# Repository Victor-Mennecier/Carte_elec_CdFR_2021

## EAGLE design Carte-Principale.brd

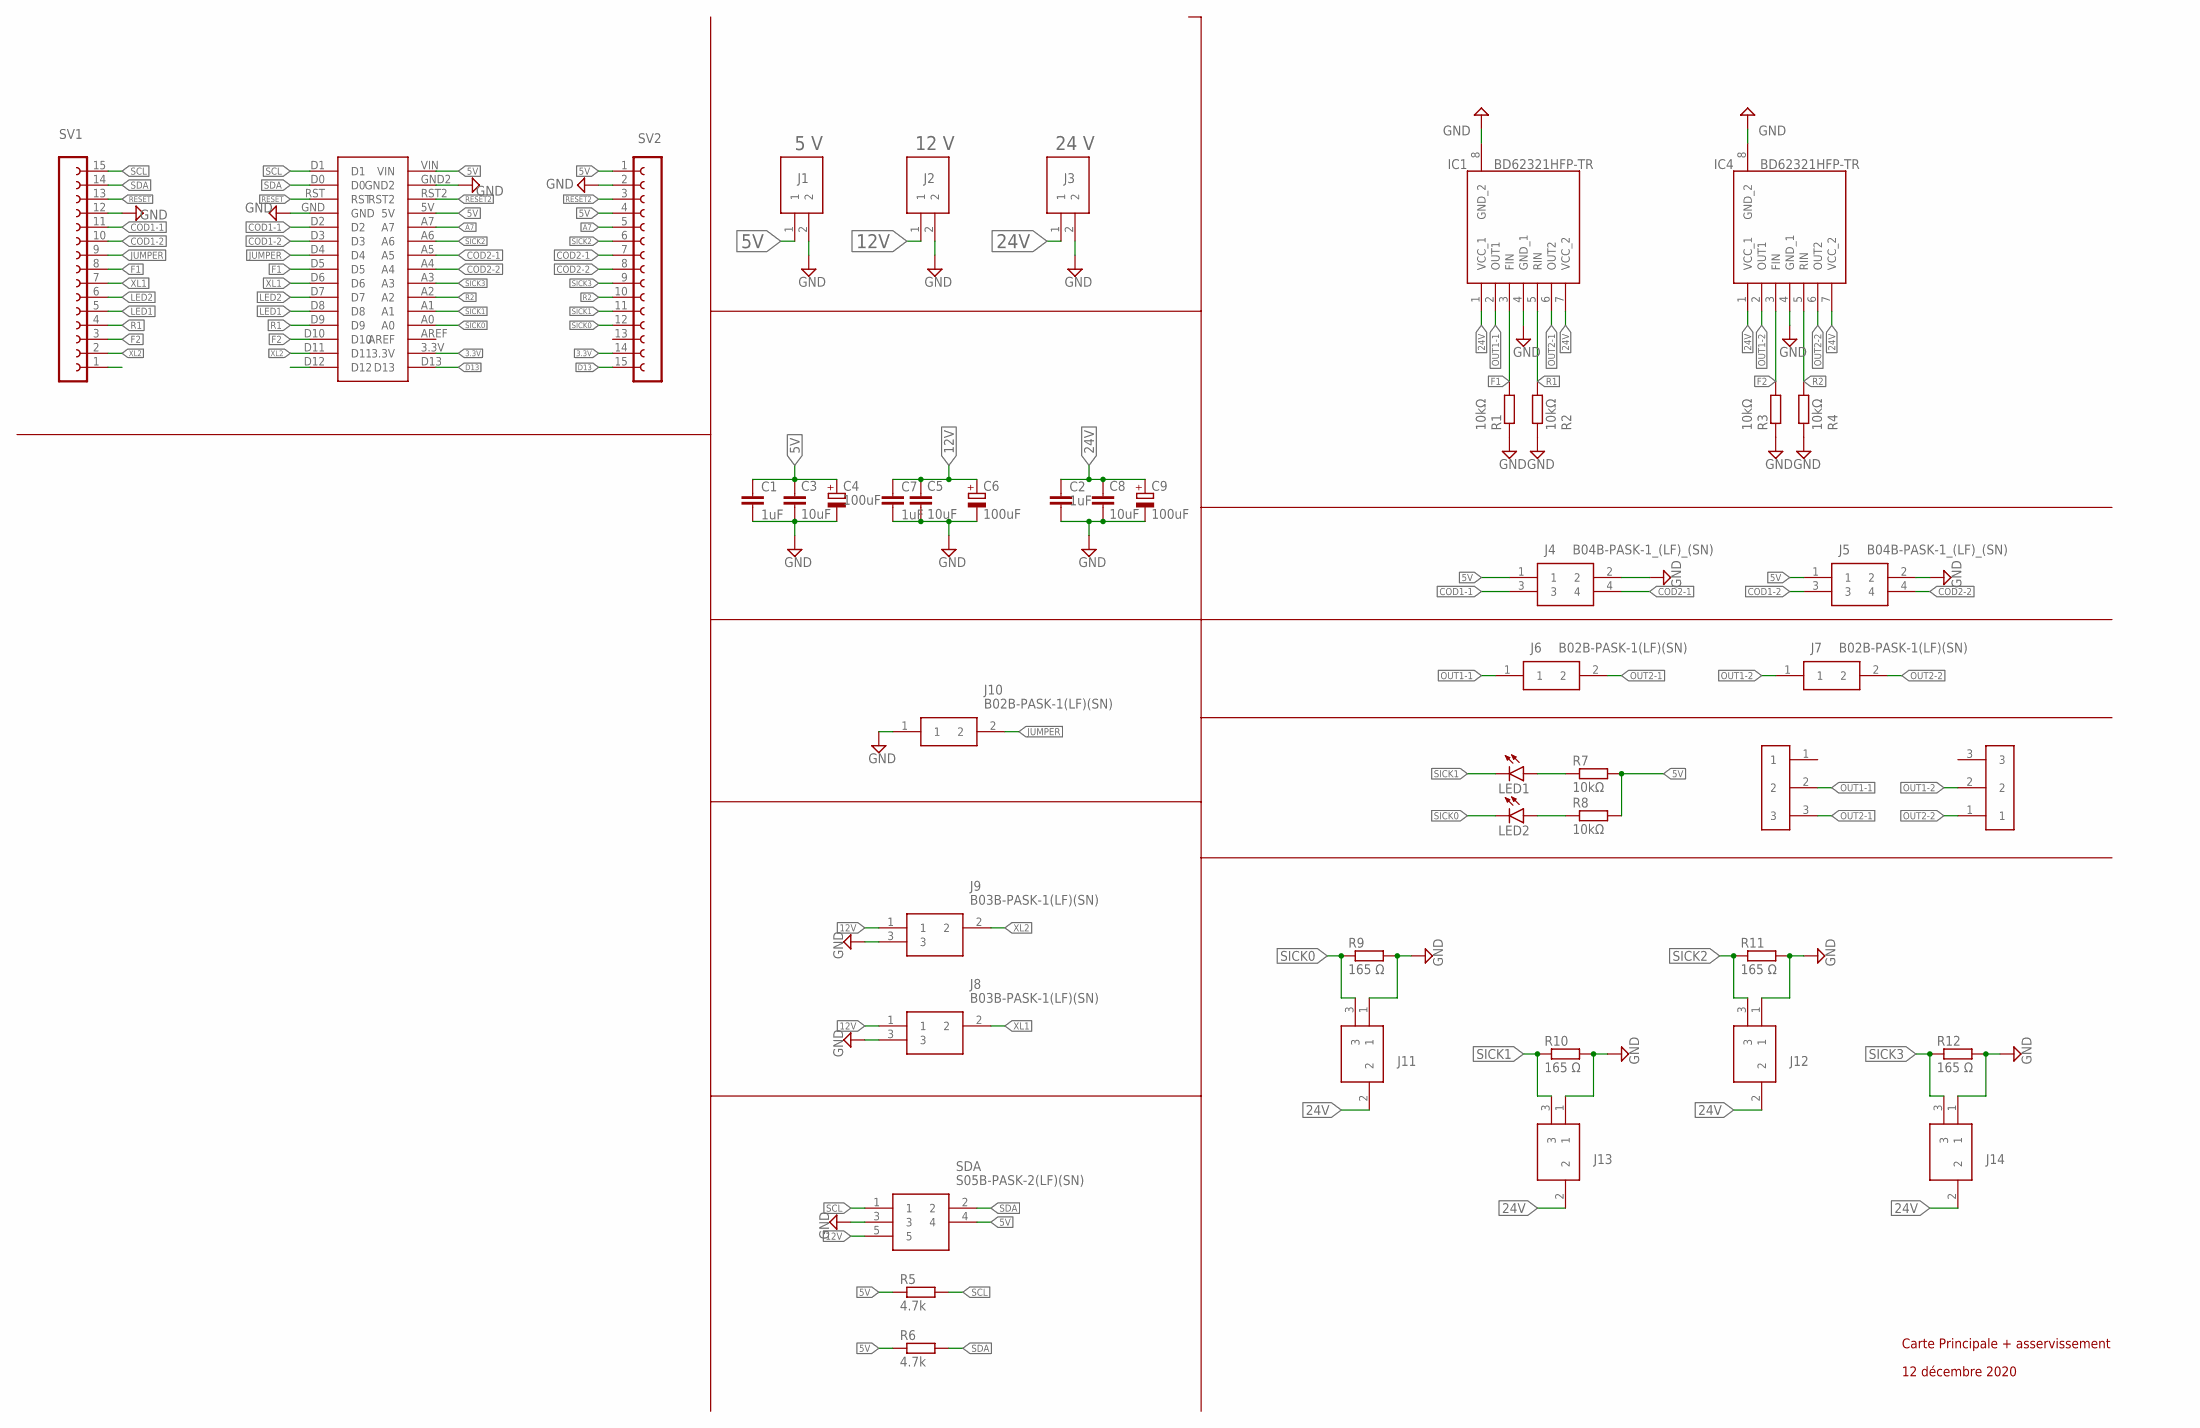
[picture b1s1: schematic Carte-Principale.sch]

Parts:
C1, C2, C7: 1uF; C0805
C3, C5, C8: 10uF; C0805
C4, C6, C9: 100uF; 153CLV-0605
IC1, IC4: BD62321HFP-TR; HRP7
J1, J2, J3: B2P-VH(LF)(SN); SHDR2W114P0X396_1X2_786X850X94
J4, J5: B04B-PASK-1_(LF)_(SN); B04B-PASK-1
J6, J7, J10: B02B-PASK-1(LF)(SN); B02BPASK1LFSN
J8, J9, J11, J12, J13, J14: B03B-PASK-1(LF)(SN); B03BPASK1LFSN
LED1, LED2: LEDCHIP-LED0805; CHIP-LED0805
R1, R2, R3, R4, R7, R8: 10kΩ; R0805
R5, R6: 4.7k; R01005
R9, R10, R11, R12: 165 Ω; R0805
SDA: S05B-PASK-2(LF)(SN)
SV1, SV2: FE15-1; FE15
U$1: STM32-L432KC
U$2, U$3: HEADER3PIN; HEADER3PINFOOTPRINT

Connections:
3.3V: SV2.14, U$1.3.3V
5V: C1.1, C3.1, C4.+, J1.1, J4.1, J5.1, R5.1, R6.1, R7.2, R8.2, SDA.4, SV2.1, SV2.4, U$1.5V, U$1.VIN
12V: C5.1, C6.+, C7.1, J2.1, J8.1, J9.1, SDA.5
24V: C2.1, C8.1, C9.+, IC1.1 (VCC_1), IC1.7 (VCC_2), IC4.1 (VCC_1), IC4.7 (VCC_2), J3.1, J11.2, J12.2, J13.2, J14.2
A7: SV2.5, U$1.A7
COD1-1: J4.3, SV1.11, U$1.D2
COD1-2: J5.3, SV1.10, U$1.D3
COD2-1: J4.4, SV2.7, U$1.A5
COD2-2: J5.4, SV2.8, U$1.A4
D13: SV2.15, U$1.D13
F1: IC1.3 (FIN), R1.2, SV1.8, U$1.D5
F2: IC4.3 (FIN), R3.2, SV1.3, U$1.D10
GND: C1.2, C2.2, C3.2, C4.-, C5.2, C6.-, C7.2, C8.2, C9.-, IC1.4 (GND_1), IC1.8 (GND_2), IC4.4 (GND_1), IC4.8 (GND_2), J1.2, J2.2, J3.2, J4.2, J5.2, J8.3, J9.3, J10.1, J11.1, J12.1, J13.1, J14.1, R1.1, R2.1, R3.1, R4.1, R9.2, R10.2, R11.2, R12.2, SDA.3, SV1.12, SV2.2, U$1.GND, U$1.GND2
JUMPER: J10.2, SV1.9, U$1.D4
LED1: SV1.5, U$1.D8
LED2: SV1.6, U$1.D7
unnamed: LED1.A, R7.1
unnamed: LED2.A, R8.1
OUT1-1: IC1.2 (OUT1), J6.1, U$2.2
OUT1-2: IC4.2 (OUT1), J7.1, U$3.2
OUT2-1: IC1.6 (OUT2), J6.2, U$2.3
OUT2-2: IC4.6 (OUT2), J7.2, U$3.1
R1: IC1.5 (RIN), R2.2, SV1.4, U$1.D9
R2: IC4.5 (RIN), R4.2, SV2.10, U$1.A2
RESET: SV1.13, U$1.RST
RESET2: SV2.3, U$1.RST2
SCL: R5.2, SDA.1, SV1.15, U$1.D1
SDA: R6.2, SDA.2, SV1.14, U$1.D0
SICK0: J11.3, LED2.C, R9.1, SV2.12, U$1.A0
SICK1: J13.3, LED1.C, R10.1, SV2.11, U$1.A1
SICK2: J12.3, R11.1, SV2.6, U$1.A6
SICK3: J14.3, R12.1, SV2.9, U$1.A3
XL1: J8.2, SV1.7, U$1.D6
XL2: J9.2, SV1.2, U$1.D11

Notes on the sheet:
Carte Principale + asservissement
12 décembre 2020
5 V
12 V
24 V

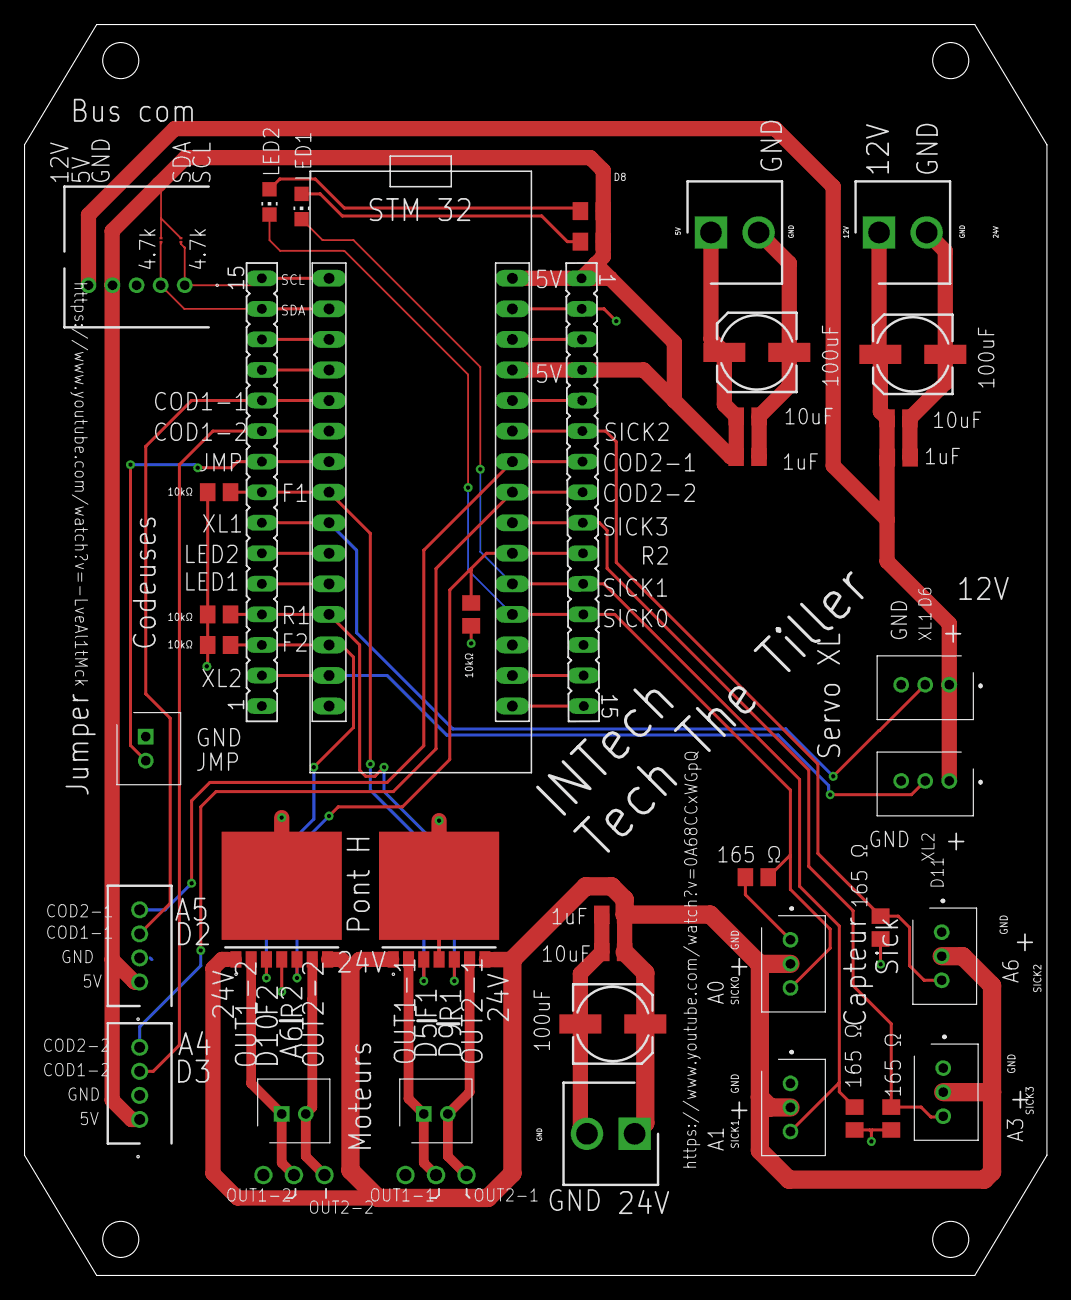
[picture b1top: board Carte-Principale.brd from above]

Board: 2 copper layers, 85.0 x 104.0 mm, 45 parts (0 on the bottom side), 34 nets.

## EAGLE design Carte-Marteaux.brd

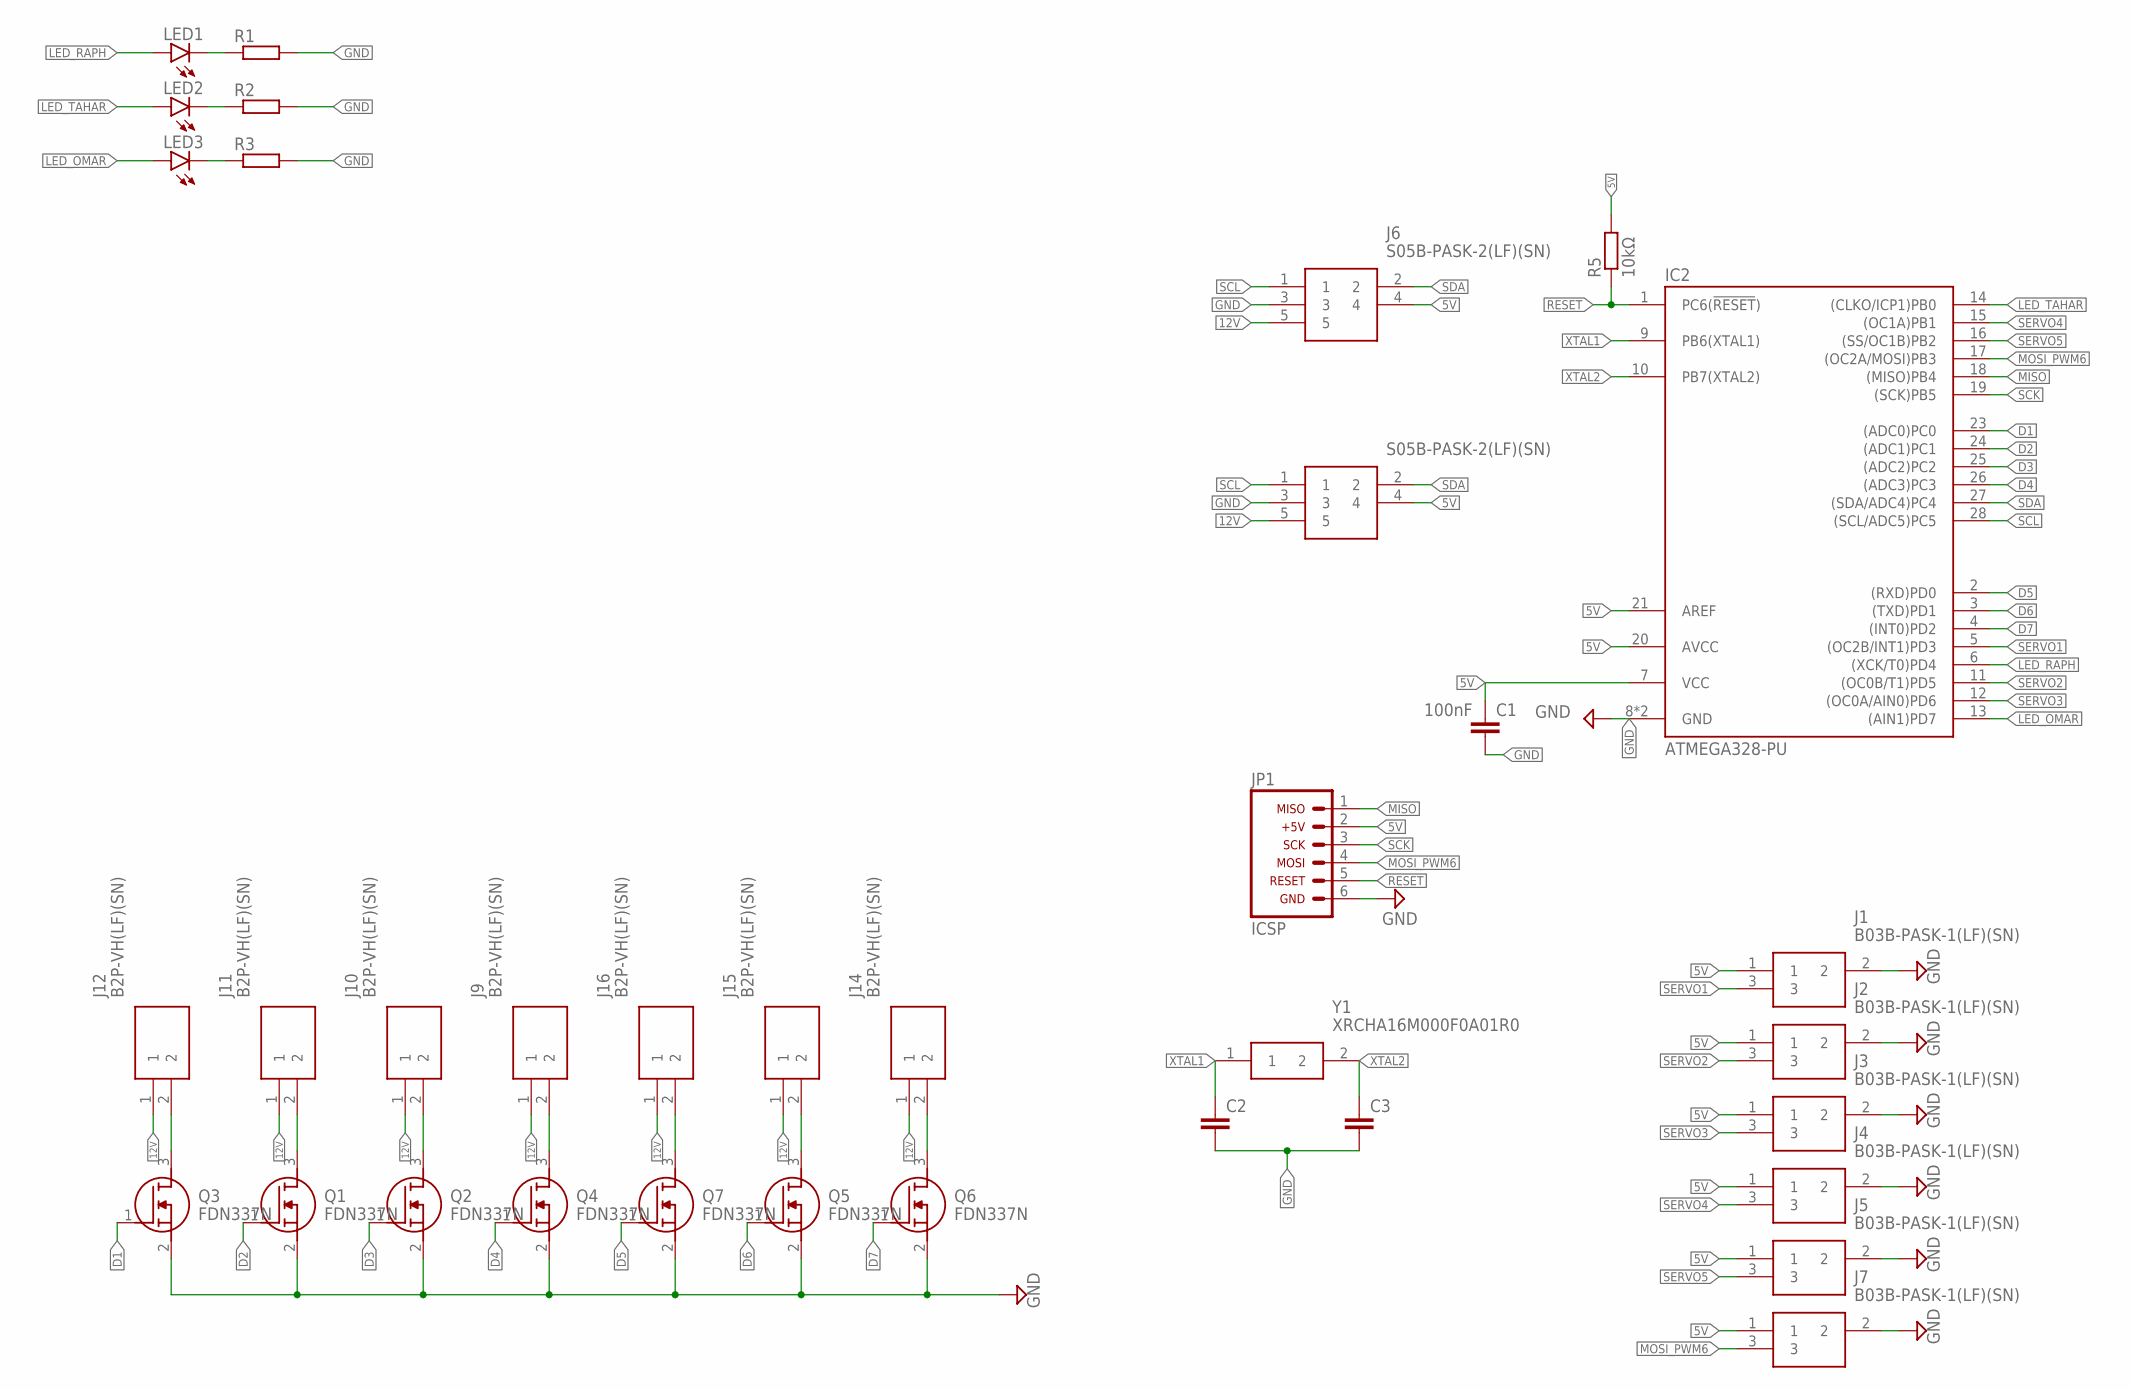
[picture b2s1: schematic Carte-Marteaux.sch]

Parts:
C1: 100nF; C0805
C2, C3: C-EUC0402; C0402
IC2: ATMEGA328-PU; DIL28
J1, J2, J3, J4, J5, J7: B03B-PASK-1(LF)(SN); B03BPASK1LFSN
J6, J8: S05B-PASK-2(LF)(SN)
J9, J10, J11, J12, J14, J15, J16: B2P-VH(LF)(SN); SHDR2W114P0X396_1X2_786X850X94
JP1: ARDUINO_CONN-ICSP; CONN-2X03
LED1, LED2, LED3: LEDCHIP-LED0805; CHIP-LED0805
Q1, Q2, Q3, Q4, Q5, Q6, Q7: FDN337N; SOT95P237X112-3N
R1, R2, R3: R-EU_R0805; R0805
R5: 10kΩ; R0805
Y1: XRCHA16M000F0A01R0; XRCHA

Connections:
5V: C1.1, IC2.7 (VCC), IC2.20 (AVCC), IC2.21 (AREF), J1.1, J2.1, J3.1, J4.1, J5.1, J6.4, J7.1, J8.4, JP1.2, R5.2
12V: J6.5, J8.5, J9.1, J10.1, J11.1, J12.1, J14.1, J15.1, J16.1
D1: IC2.23 ((ADC0)PC0), Q3.1 (G)
D2: IC2.24 ((ADC1)PC1), Q1.1 (G)
D3: IC2.25 ((ADC2)PC2), Q2.1 (G)
D4: IC2.26 ((ADC3)PC3), Q4.1 (G)
D5: IC2.2 ((RXD)PD0), Q7.1 (G)
D6: IC2.3 ((TXD)PD1), Q5.1 (G)
D7: IC2.4 ((INT0)PD2), Q6.1 (G)
GND: C1.2, C2.2, C3.2, IC2.8 (GND), IC2.22 (GND), J1.2, J2.2, J3.2, J4.2, J5.2, J6.3, J7.2, J8.3, JP1.6, Q1.2 (S), Q2.2 (S), Q3.2 (S), Q4.2 (S), Q5.2 (S), Q6.2 (S), Q7.2 (S), R1.2, R2.2, R3.2
LED_OMAR: IC2.13 ((AIN1)PD7), LED3.A
LED_RAPH: IC2.6 ((XCK/T0)PD4), LED1.A
LED_TAHAR: IC2.14 ((CLKO/ICP1)PB0), LED2.A
MISO: IC2.18 ((MISO)PB4), JP1.1
MOSI_PWM6: IC2.17 ((OC2A/MOSI)PB3), J7.3, JP1.4
unnamed: LED1.C, R1.1
unnamed: LED2.C, R2.1
unnamed: LED3.C, R3.1
unnamed: J12.2, Q3.3 (D)
unnamed: J11.2, Q1.3 (D)
unnamed: J10.2, Q2.3 (D)
unnamed: J9.2, Q4.3 (D)
unnamed: J16.2, Q7.3 (D)
unnamed: J15.2, Q5.3 (D)
unnamed: J14.2, Q6.3 (D)
RESET: IC2.1 (PC6(!RESET!)), JP1.5, R5.1
SCK: IC2.19 ((SCK)PB5), JP1.3
SCL: IC2.28 ((SCL/ADC5)PC5), J6.1, J8.1
SDA: IC2.27 ((SDA/ADC4)PC4), J6.2, J8.2
SERVO1: IC2.5 ((OC2B/INT1)PD3), J1.3
SERVO2: IC2.11 ((OC0B/T1)PD5), J2.3
SERVO3: IC2.12 ((OC0A/AIN0)PD6), J3.3
SERVO4: IC2.15 ((OC1A)PB1), J4.3
SERVO5: IC2.16 ((SS/OC1B)PB2), J5.3
XTAL1: C2.1, IC2.9 (PB6(XTAL1)), Y1.1
XTAL2: C3.1, IC2.10 (PB7(XTAL2)), Y1.2

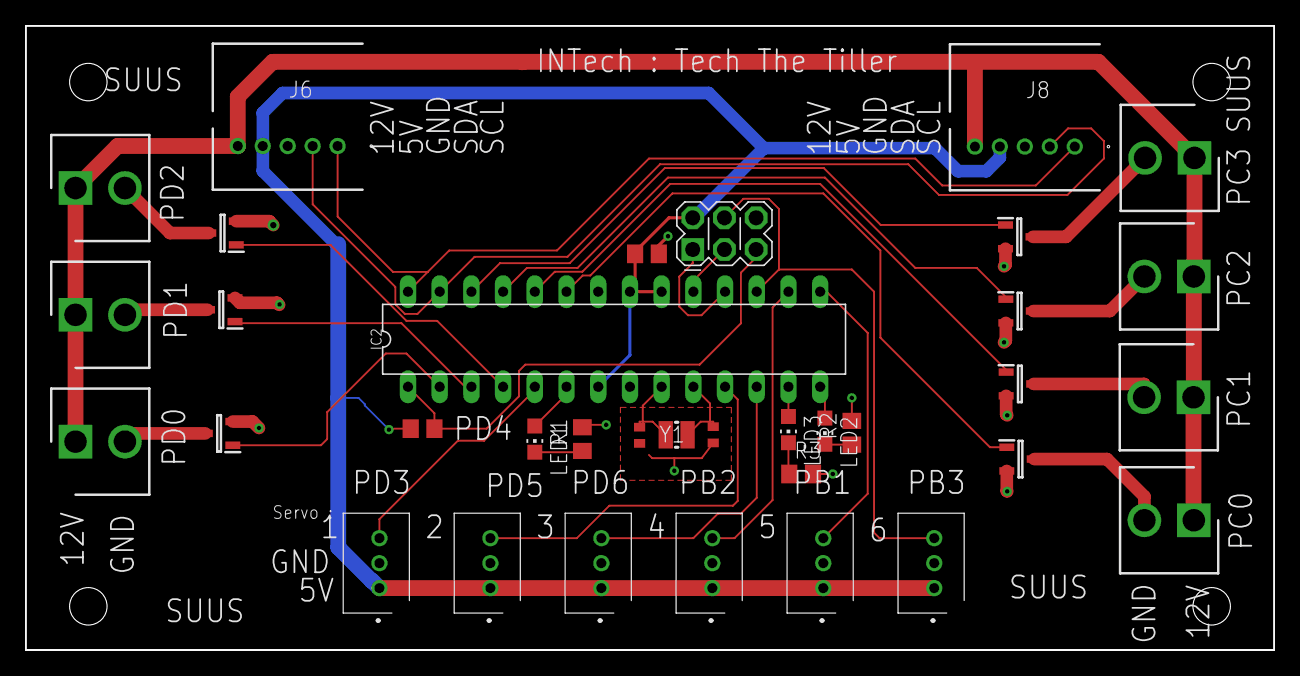
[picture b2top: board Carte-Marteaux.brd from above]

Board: 2 copper layers, 100.0 x 50.0 mm, 35 parts (0 on the bottom side), 36 nets.

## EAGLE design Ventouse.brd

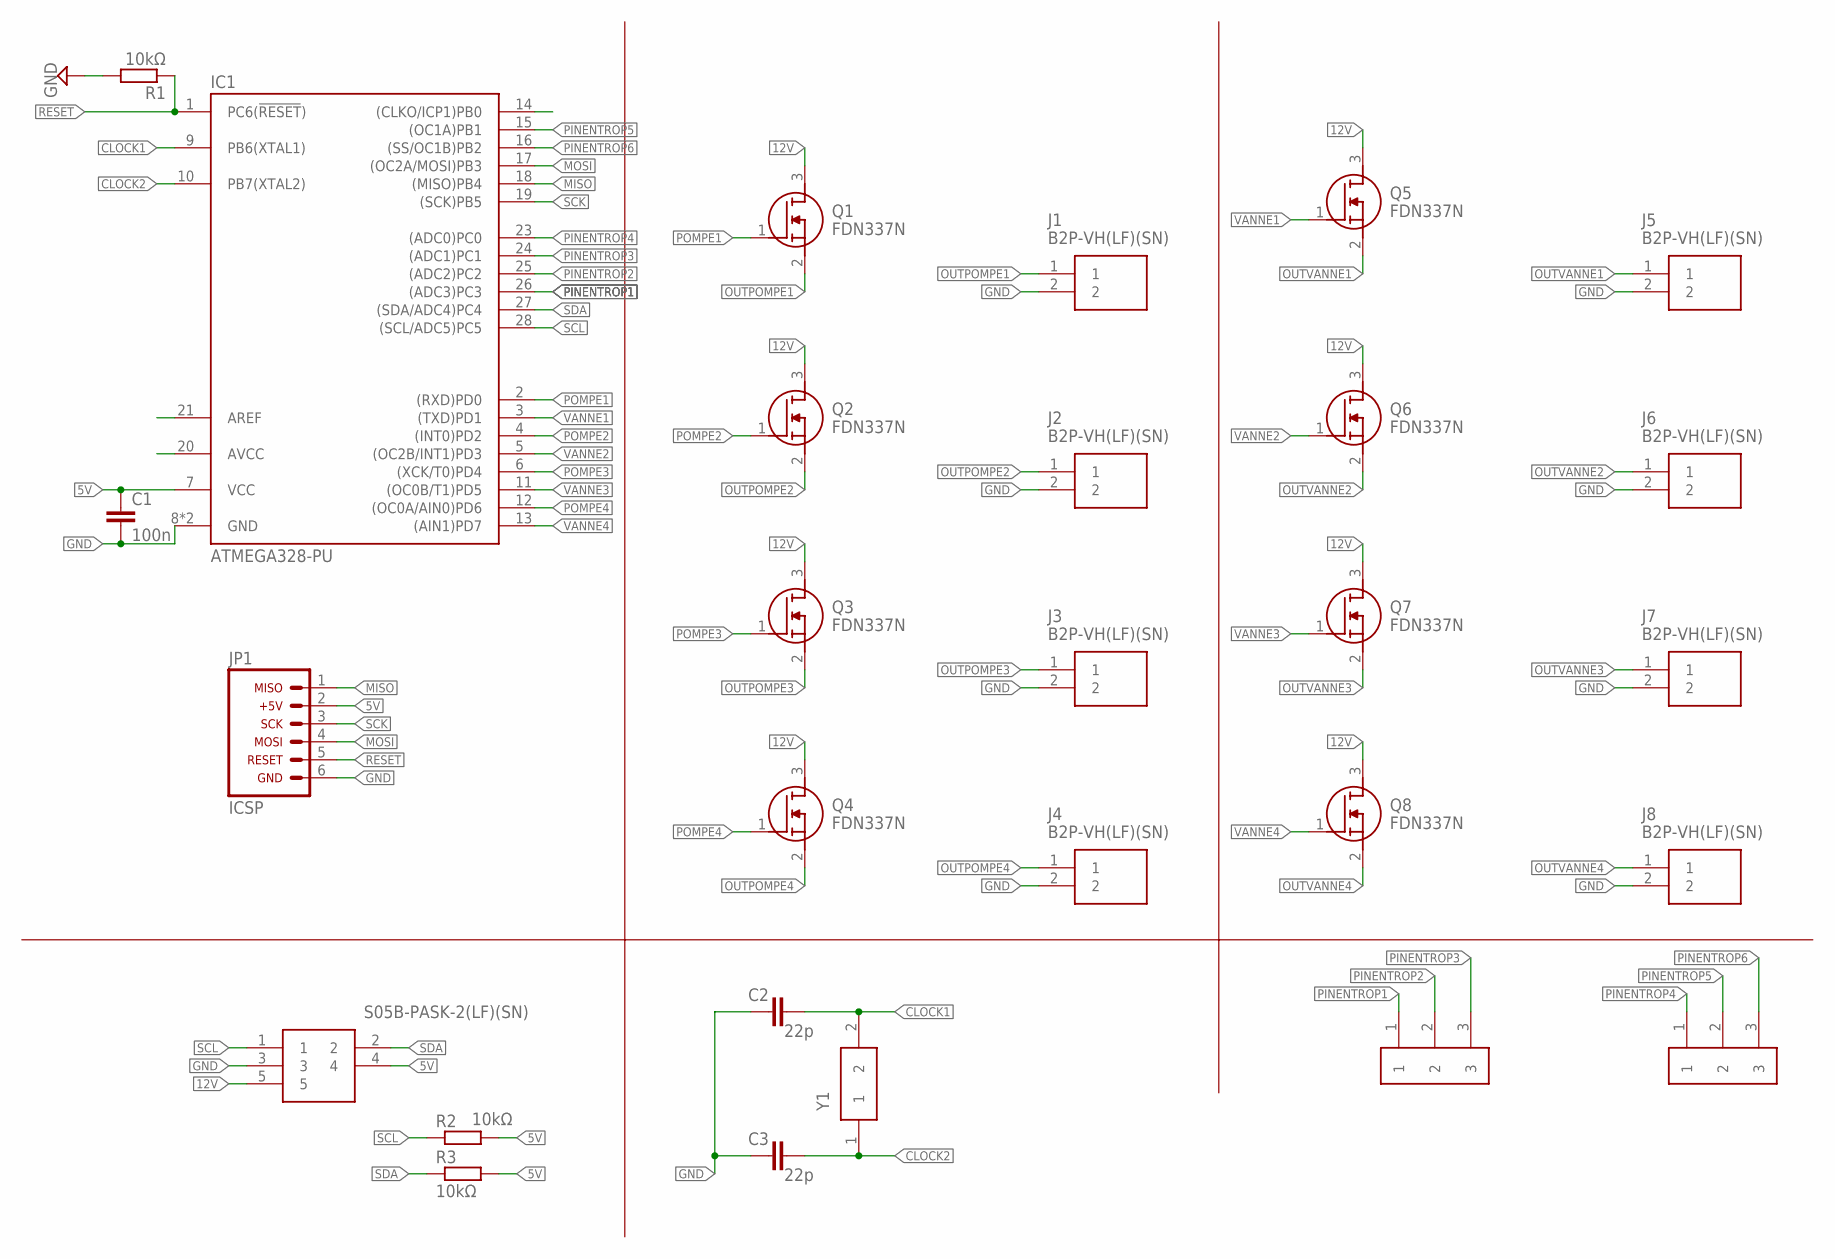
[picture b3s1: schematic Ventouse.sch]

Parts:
C1: 100n; C0805
C2, C3: 22p; C0805
IC1: ATMEGA328-PU; DIL28
J1, J2, J3, J4, J5, J6, J7, J8: B2P-VH(LF)(SN); SHDR2W114P0X396_1X2_786X850X94
JP1: ARDUINO_CONN-ICSP; CONN-2X03
Q1, Q2, Q3, Q4, Q5, Q6, Q7, Q8: FDN337N; SOT95P237X112-3N
R1, R2, R3: 10kΩ; R0805
SCL: S05B-PASK-2(LF)(SN)
U$1, U$2: HEADER3PIN; HEADER3PINFOOTPRINT
Y1: XRCHA16M000F0A01R0; XRCHA

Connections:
5V: C1.1, IC1.7 (VCC), JP1.2, R2.2, R3.2, SCL.4
12V: Q1.3 (D), Q2.3 (D), Q3.3 (D), Q4.3 (D), Q5.3 (D), Q6.3 (D), Q7.3 (D), Q8.3 (D), SCL.5
CLOCK1: C2.2, IC1.9 (PB6(XTAL1)), Y1.2
CLOCK2: C3.2, IC1.10 (PB7(XTAL2)), Y1.1
GND: C1.2, C2.1, C3.1, IC1.8 (GND), IC1.22 (GND), J1.2, J2.2, J3.2, J4.2, J5.2, J6.2, J7.2, J8.2, JP1.6, R1.2, SCL.3
MISO: IC1.18 ((MISO)PB4), JP1.1
MOSI: IC1.17 ((OC2A/MOSI)PB3), JP1.4
OUTPOMPE1: J1.1, Q1.2 (S)
OUTPOMPE2: J2.1, Q2.2 (S)
OUTPOMPE3: J3.1, Q3.2 (S)
OUTPOMPE4: J4.1, Q4.2 (S)
OUTVANNE1: J5.1, Q5.2 (S)
OUTVANNE2: J6.1, Q6.2 (S)
OUTVANNE3: J7.1, Q7.2 (S)
OUTVANNE4: J8.1, Q8.2 (S)
PINENTROP1: IC1.26 ((ADC3)PC3), U$1.1
PINENTROP2: IC1.25 ((ADC2)PC2), U$1.2
PINENTROP3: IC1.24 ((ADC1)PC1), U$1.3
PINENTROP4: IC1.23 ((ADC0)PC0), U$2.1
PINENTROP5: IC1.15 ((OC1A)PB1), IC1.21 (AREF), U$2.2
PINENTROP6: IC1.16 ((SS/OC1B)PB2), IC1.20 (AVCC), U$2.3
POMPE1: IC1.2 ((RXD)PD0), Q1.1 (G)
POMPE2: IC1.4 ((INT0)PD2), Q2.1 (G)
POMPE3: IC1.6 ((XCK/T0)PD4), Q3.1 (G)
POMPE4: IC1.12 ((OC0A/AIN0)PD6), Q4.1 (G)
RESET: IC1.1 (PC6(!RESET!)), JP1.5, R1.1
SCK: IC1.19 ((SCK)PB5), JP1.3
SCL: IC1.28 ((SCL/ADC5)PC5), R2.1, SCL.1
SDA: IC1.27 ((SDA/ADC4)PC4), R3.1, SCL.2
VANNE1: IC1.3 ((TXD)PD1), Q5.1 (G)
VANNE2: IC1.5 ((OC2B/INT1)PD3), Q6.1 (G)
VANNE3: IC1.11 ((OC0B/T1)PD5), Q7.1 (G)
VANNE4: IC1.13 ((AIN1)PD7), Q8.1 (G)

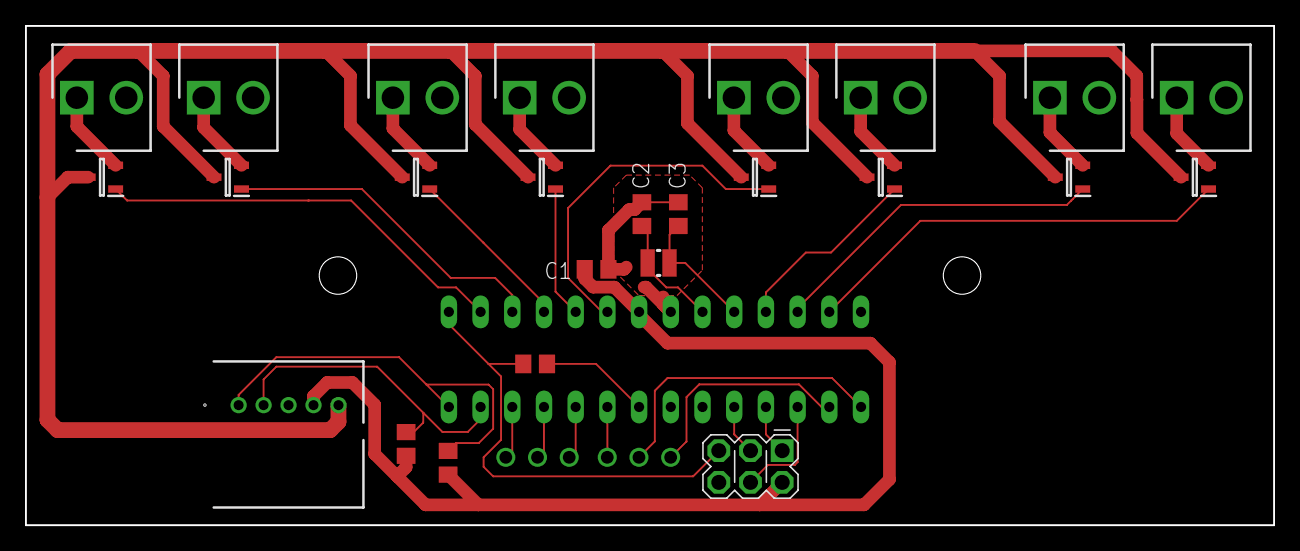
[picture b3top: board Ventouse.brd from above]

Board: 2 copper layers, 100.0 x 40.0 mm, 28 parts (1 on the bottom side), 33 nets.

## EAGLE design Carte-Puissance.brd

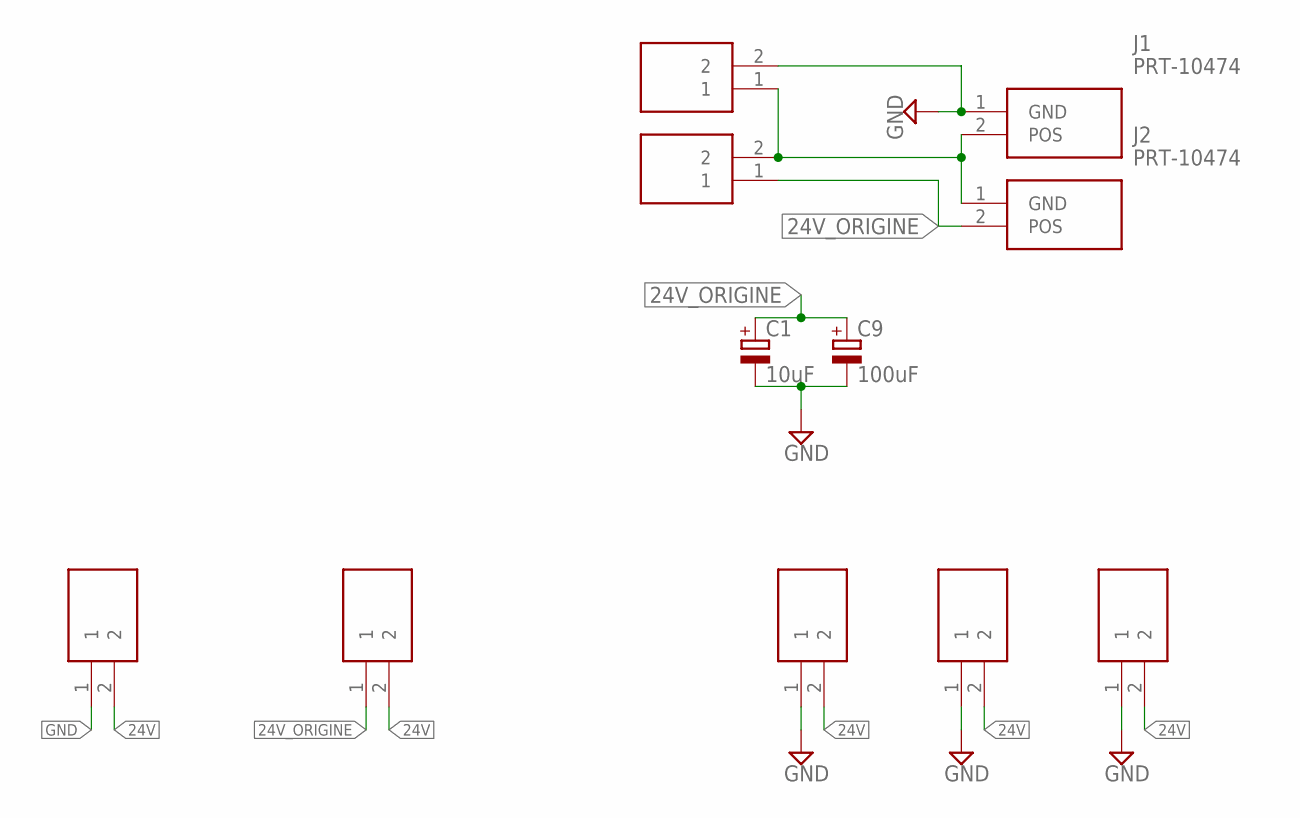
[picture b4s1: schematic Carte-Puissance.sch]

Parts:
C1: 10uF; 150CLZ-0810
C9: 100uF; 150CLZ-0810
J1, J2: PRT-10474; SHDR2W320P716_1X2_1574X813X158
J3, J4, J5, J6, J7, J8, J9: B2P-VH(LF)(SN); SHDR2W114P0X396_1X2_786X850X94

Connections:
24V: J3.2, J4.2, J5.2, J6.2, J7.2
24V_ORIGINE: C1.+, C9.+, J2.2 (POS), J6.1, J8.1
GND: C1.-, C9.-, J1.1 (GND), J3.1, J4.1, J5.1, J7.1, J9.2
unnamed: J1.2 (POS), J2.1 (GND), J8.2, J9.1

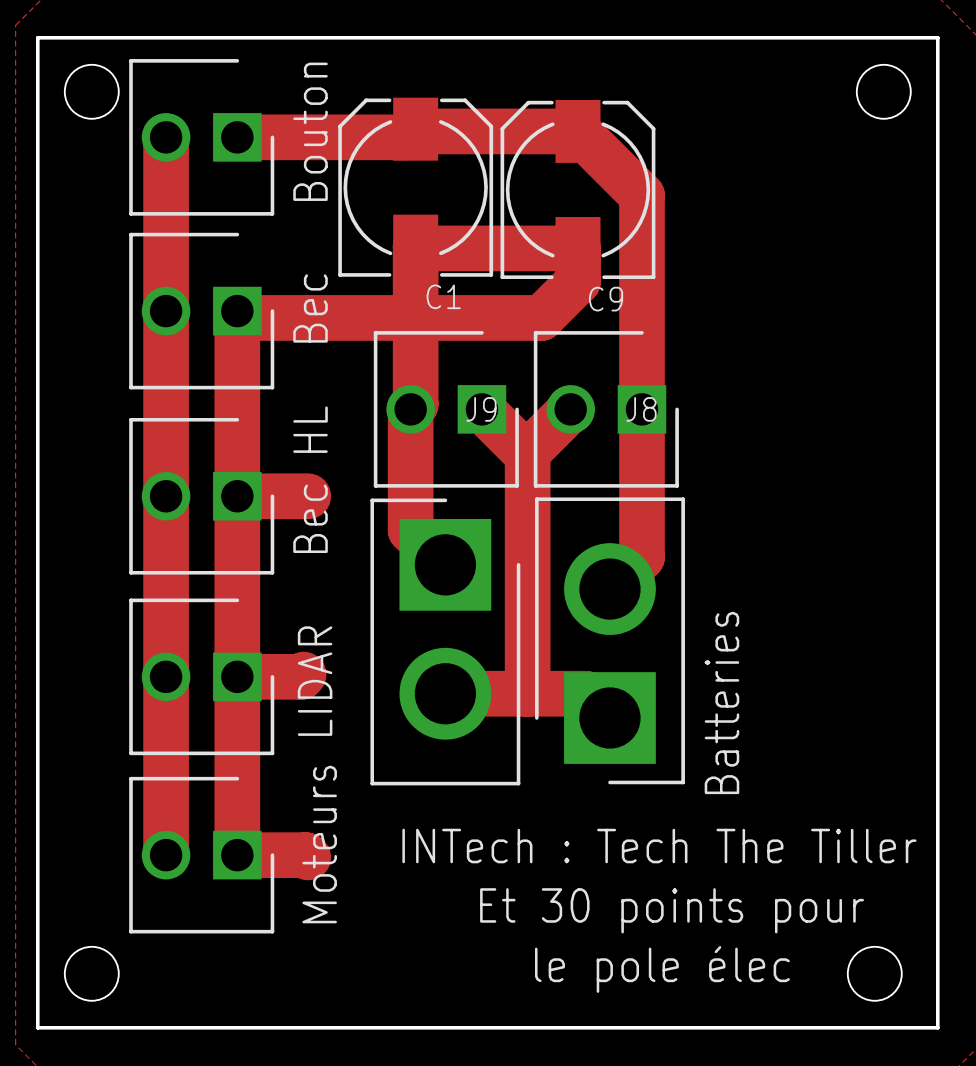
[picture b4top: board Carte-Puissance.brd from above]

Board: 2 copper layers, 50.0 x 55.0 mm, 11 parts (0 on the bottom side), 4 nets.

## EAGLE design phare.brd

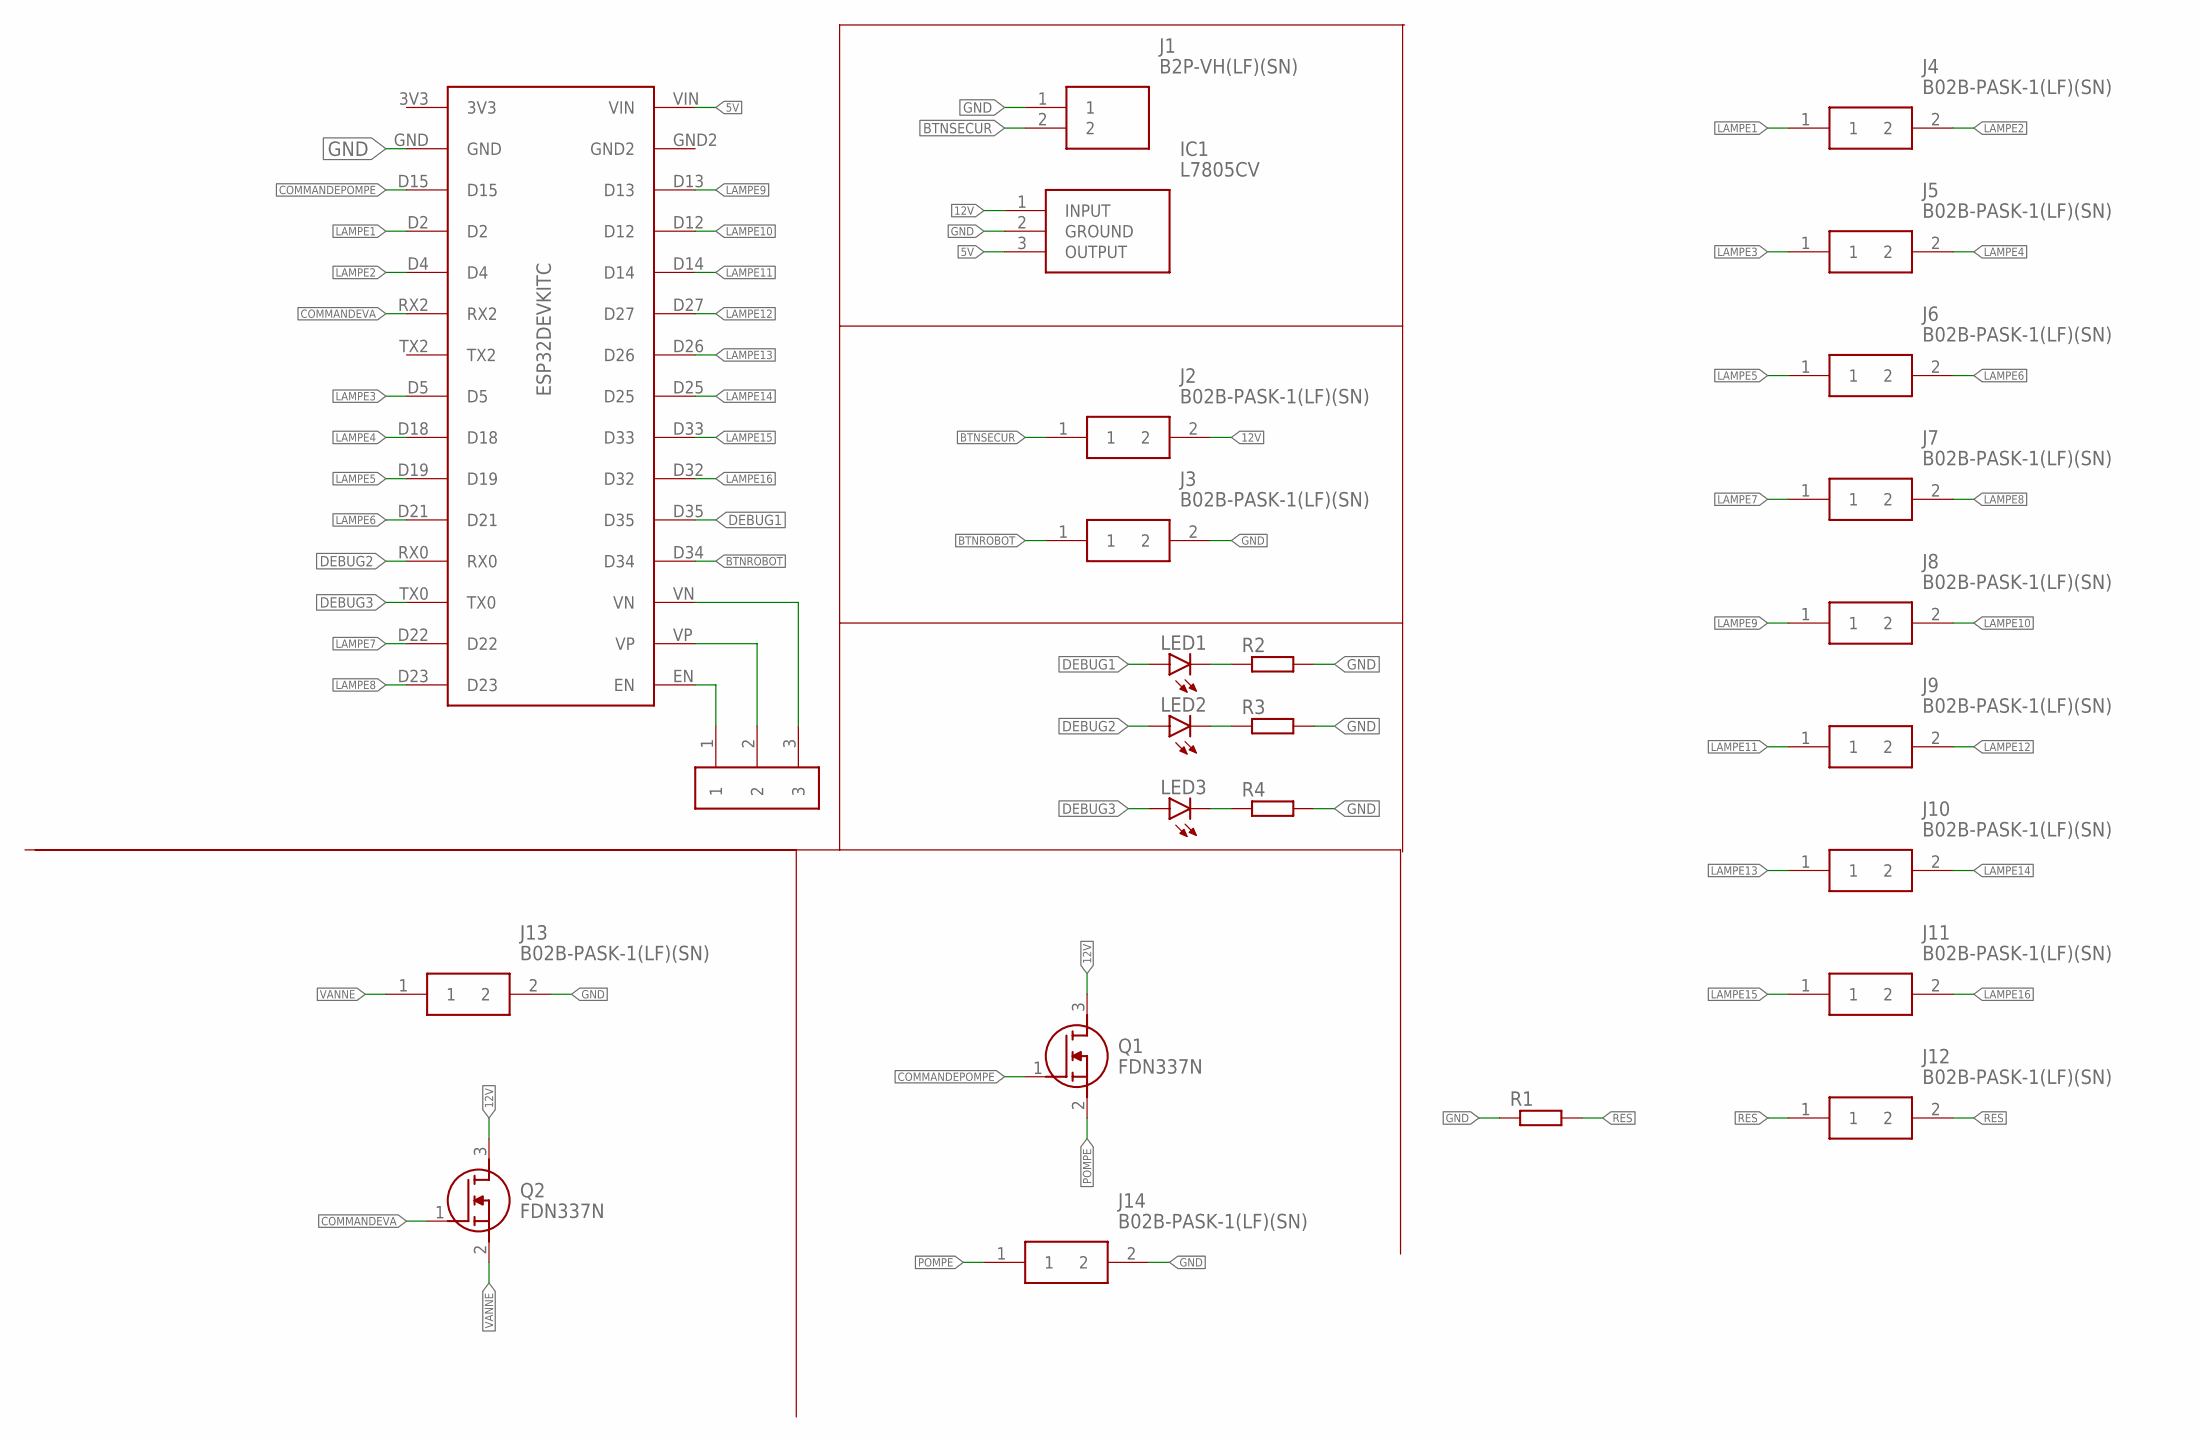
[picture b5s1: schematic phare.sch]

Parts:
IC1: L7805CV; TO255P460X1020X2008-3P
J1: B2P-VH(LF)(SN); SHDR2W114P0X396_1X2_786X850X94
J2, J3, J4, J5, J6, J7, J8, J9, J10, J11, J12, J13, J14: B02B-PASK-1(LF)(SN); B02BPASK1LFSN
LED1, LED2, LED3: LEDCHIP-LED0805; CHIP-LED0805
Q1, Q2: FDN337N; SOT95P237X112-3N
R1, R2, R3, R4: R-EU_R0805; R0805
U$1: ESP32DEVKITC; ESP32FOOTPRINT
U$2: HEADER3PIN; HEADER3PINFOOTPRINT

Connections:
5V: IC1.3 (OUTPUT), U$1.VIN
12V: IC1.1 (INPUT), J2.2, Q1.3 (D), Q2.3 (D)
BTNROBOT: J3.1, U$1.D34
BTNSECUR: J1.2, J2.1
COMMANDEPOMPE: Q1.1 (G), U$1.D15
COMMANDEVA: Q2.1 (G), U$1.RX2
DEBUG1: LED1.A, U$1.D35
DEBUG2: LED2.A, U$1.RX0
DEBUG3: LED3.A, U$1.TX0
GND: IC1.2 (GROUND), J1.1, J3.2, J13.2, J14.2, R1.1, R2.2, R3.2, R4.2, U$1.GND
LAMPE1: J4.1, U$1.D2
LAMPE2: J4.2, U$1.D4
LAMPE3: J5.1, U$1.D5
LAMPE4: J5.2, U$1.D18
LAMPE5: J6.1, U$1.D19
LAMPE6: J6.2, U$1.D21
LAMPE7: J7.1, U$1.D22
LAMPE8: J7.2, U$1.D23
LAMPE9: J8.1, U$1.D13
LAMPE10: J8.2, U$1.D12
LAMPE11: J9.1, U$1.D14
LAMPE12: J9.2, U$1.D27
LAMPE13: J10.1, U$1.D26
LAMPE14: J10.2, U$1.D25
LAMPE15: J11.1, U$1.D33
LAMPE16: J11.2, U$1.D32
unnamed: LED1.C, R2.1
unnamed: LED2.C, R3.1
unnamed: LED3.C, R4.1
unnamed: U$1.EN, U$2.1
unnamed: U$1.VP, U$2.2
unnamed: U$1.VN, U$2.3
POMPE: J14.1, Q1.2 (S)
RES: J12.1, J12.2, R1.2
VANNE: J13.1, Q2.2 (S)

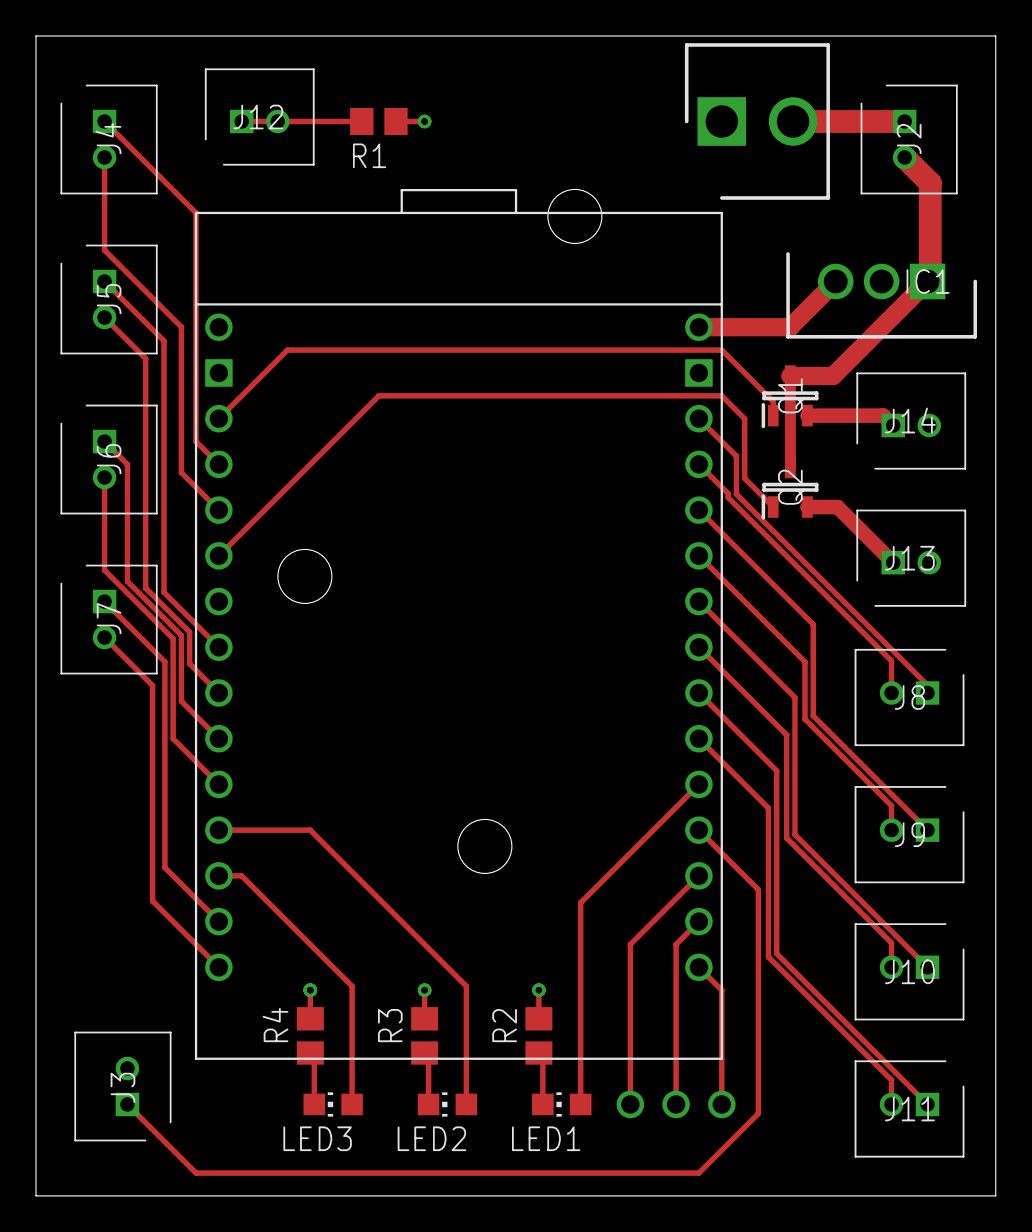
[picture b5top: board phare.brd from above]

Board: 2 copper layers, 53.3 x 64.4 mm, 26 parts (0 on the bottom side), 35 nets.
